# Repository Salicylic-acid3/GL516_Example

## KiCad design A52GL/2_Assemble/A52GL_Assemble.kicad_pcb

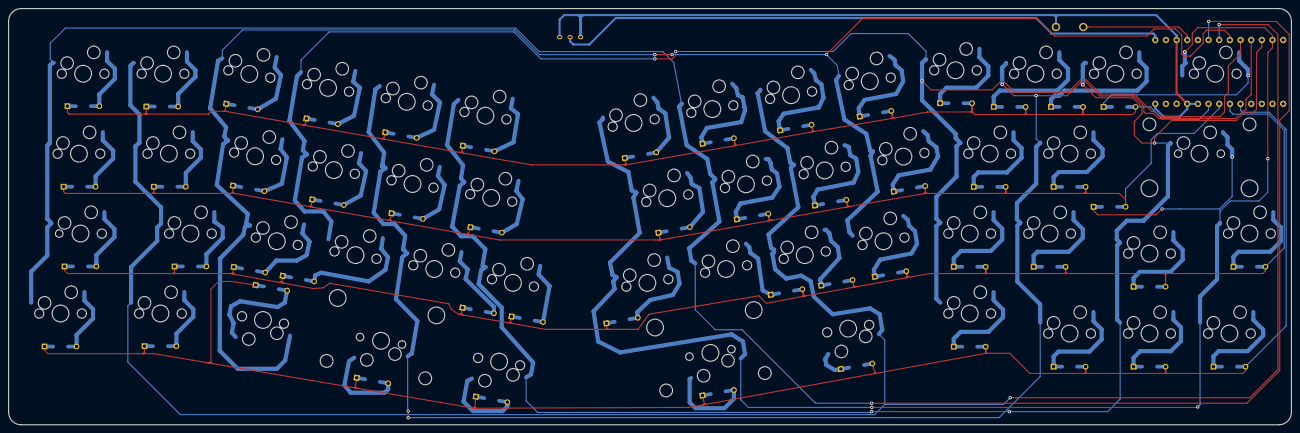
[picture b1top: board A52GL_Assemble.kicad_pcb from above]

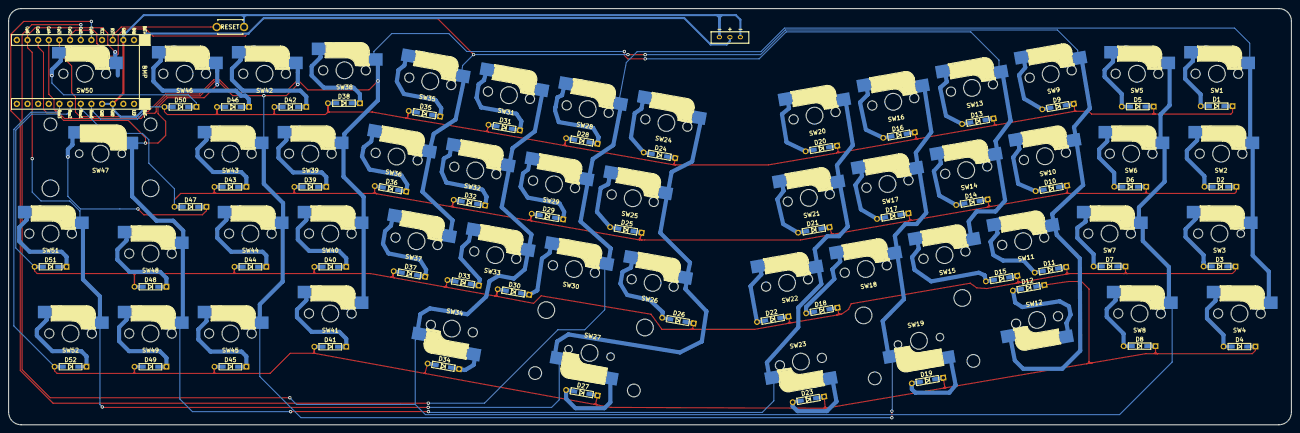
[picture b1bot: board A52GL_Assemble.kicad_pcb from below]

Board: 2 copper layers, 305.8 x 99.2 mm, 107 parts (2 on the bottom side), 66 nets.

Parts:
D1, D2, D3, D4, D5, D6, D7, D8, D9, D10, D11, D12, D13, D14, D15, D16, D17, D18, D19, D20, D21, D22, D23, D24, D25, D26, D27, D28, D29, D30, D31, D32, D33, D34, D35, D36, D37, D38, D39, D40, D41, D42, D43, D44, D45, D46, D47, D48, D49, D50, D51, D52: D; Diode_TH_SMD
J1: Conn_01x02; Battery_XH2.5_GL
SW1, SW5, SW6, SW7, SW9, SW10, SW11, SW12, SW13, SW14, SW15, SW16, SW17, SW18, SW20, SW21, SW22, SW23, SW24, SW25, SW26, SW28, SW29, SW30, SW31, SW32, SW33, SW35, SW36, SW37, SW38, SW39, SW40, SW41, SW42, SW43, SW44, SW45, SW46, SW48, SW49, SW51, SW52: SW_PUSH; CherryMX_Hotswap_1.0u
SW2, SW4, SW8, SW34: SW_PUSH; CherryMX_Hotswap_1.25u
SW3: SW_PUSH; CherryMX_Hotswap_1.75u
SW19: SW_PUSH; CherryMX_Hotswap_2u
SW27, SW47: SW_PUSH; CherryMX_Hotswap_2.25u
SW50: SW_PUSH; CherryMX_Hotswap_BL_LH_v2_
SW53: SW_PUSH; ResetSW
U1: BLEMicroPro; Micon_BMP_GL

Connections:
Bat+: J1.1, U1.25
Col0: SW1.1, SW2.1, SW3.1, SW4.1, SW28.1, SW29.1, SW30.1, U1.20
Col1: SW5.1, SW6.1, SW7.1, SW8.1, SW31.1, SW32.1, SW33.1, SW34.1, U1.19
Col2: SW9.1, SW10.1, SW11.1, SW12.1, SW35.1, SW36.1, SW37.1, U1.18
Col3: SW13.1, SW14.1, SW15.1, SW38.1, SW39.1, SW40.1, SW41.1, U1.17
Col4: SW16.1, SW17.1, SW18.1, SW19.1, SW42.1, SW43.1, SW44.1, SW45.1, U1.16
Col5: SW20.1, SW21.1, SW22.1, SW23.1, SW46.1, SW47.1, SW48.1, SW49.1, U1.15
Col6: SW24.1, SW25.1, SW26.1, SW27.1, SW50.1, SW51.1, SW52.1, U1.14
GND: J1.2, SW53.2, U1.3, U1.4, U1.23, U1.26
unnamed: D1.2, SW1.2
unnamed: D2.2, SW2.2
unnamed: D3.2, SW3.2
unnamed: D4.2, SW4.2
unnamed: D5.2, SW5.2
unnamed: D6.2, SW6.2
unnamed: D7.2, SW7.2
unnamed: D8.2, SW8.2
unnamed: D9.2, SW9.2
unnamed: D10.2, SW10.2
unnamed: D11.2, SW11.2
unnamed: D12.2, SW12.2
unnamed: D13.2, SW13.2
unnamed: D14.2, SW14.2
unnamed: D15.2, SW15.2
unnamed: D16.2, SW16.2
unnamed: D17.2, SW17.2
unnamed: D18.2, SW18.2
unnamed: D19.2, SW19.2
unnamed: D20.2, SW20.2
unnamed: D21.2, SW21.2
unnamed: D22.2, SW22.2
unnamed: D23.2, SW23.2
unnamed: D24.2, SW24.2
unnamed: D25.2, SW25.2
unnamed: D26.2, SW26.2
unnamed: D27.2, SW27.2
unnamed: D28.1, SW28.2
unnamed: D29.1, SW29.2
unnamed: D30.1, SW30.2
unnamed: D31.1, SW31.2
unnamed: D32.1, SW32.2
unnamed: D33.1, SW33.2
unnamed: D34.1, SW34.2
unnamed: D35.1, SW35.2
unnamed: D36.1, SW36.2
unnamed: D37.1, SW37.2
unnamed: D38.1, SW38.2
unnamed: D39.1, SW39.2
unnamed: D40.1, SW40.2
unnamed: D41.1, SW41.2
unnamed: D42.1, SW42.2
unnamed: D43.1, SW43.2
unnamed: D44.1, SW44.2
unnamed: D45.1, SW45.2
unnamed: D46.1, SW46.2
unnamed: D47.1, SW47.2
unnamed: D48.1, SW48.2
unnamed: D49.1, SW49.2
unnamed: D50.1, SW50.2
unnamed: D51.1, SW51.2
unnamed: D52.1, SW52.2
Reset: SW53.1, U1.22
Row0: D1.1, D5.1, D9.1, D13.1, D16.1, D20.1, D24.1, D28.2, D31.2, D35.2, D38.2, D42.2, D46.2, D50.2, U1.5
Row1: D2.1, D6.1, D10.1, D14.1, D17.1, D21.1, D25.1, D29.2, D32.2, D36.2, D39.2, D43.2, D47.2, U1.6
Row2: D3.1, D7.1, D11.1, D15.1, D18.1, D22.1, D26.1, D30.2, D33.2, D37.2, D40.2, D44.2, D48.2, D51.2, U1.7
Row3: D4.1, D8.1, D12.1, D19.1, D23.1, D27.1, D34.2, D41.2, D45.2, D49.2, D52.2, U1.8

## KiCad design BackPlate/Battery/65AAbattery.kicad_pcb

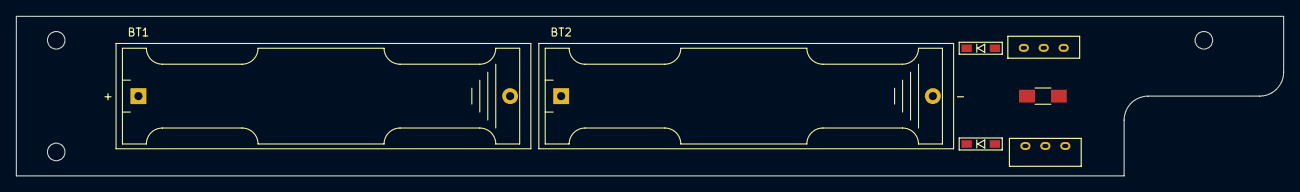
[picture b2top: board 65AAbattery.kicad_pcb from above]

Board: 2 copper layers, 158.9 x 20.0 mm, 9 parts (1 on the bottom side), 5 nets, no tracks yet.

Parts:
BT1, BT2: Battery_Cell; BatteryHolder_単4_Rev
D1, D2: D; D3_SMD
J1: Conn_01x02; XH2.5_rev
J2, J3, J4: Conn_01x01; HOLE_m2
SW1: SW_Push_SPDT; MSK-12D19_r

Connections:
Bat+: J1.1, SW1.1
GND: BT1.2, BT2.2, J1.2
unnamed: BT1.1, D1.2
unnamed: BT2.1, D2.2
unnamed: D1.1, D2.1, SW1.2
